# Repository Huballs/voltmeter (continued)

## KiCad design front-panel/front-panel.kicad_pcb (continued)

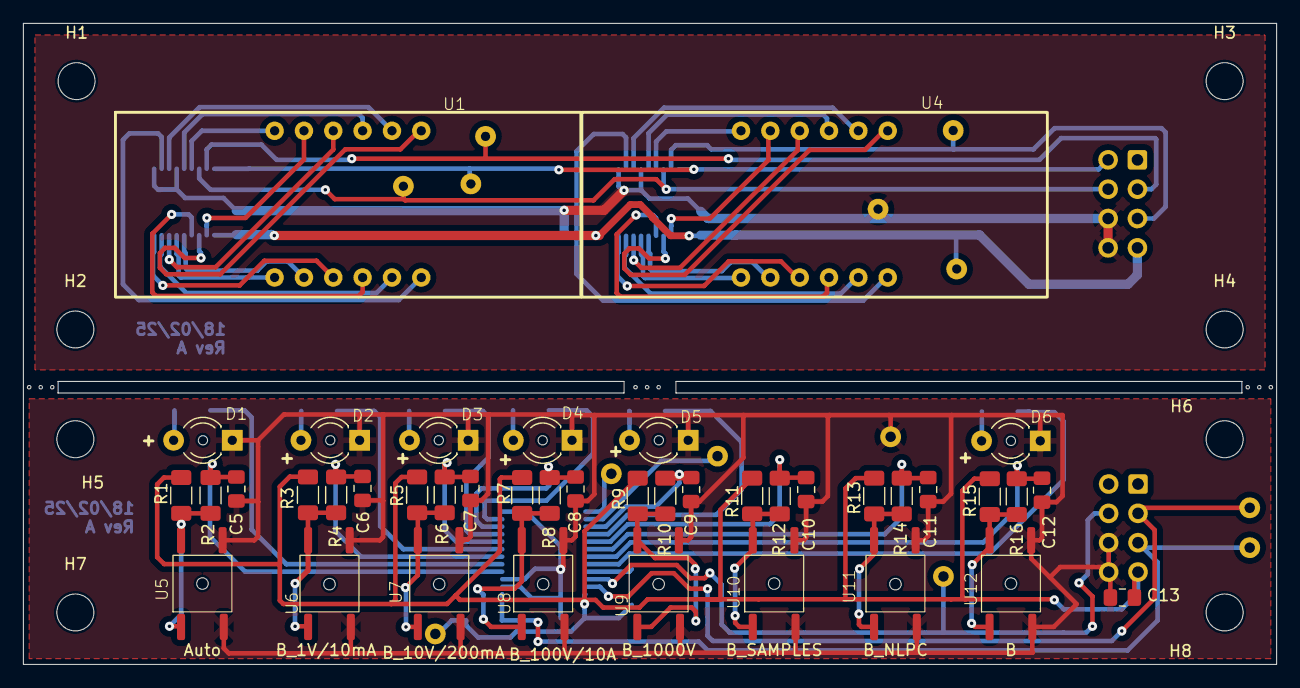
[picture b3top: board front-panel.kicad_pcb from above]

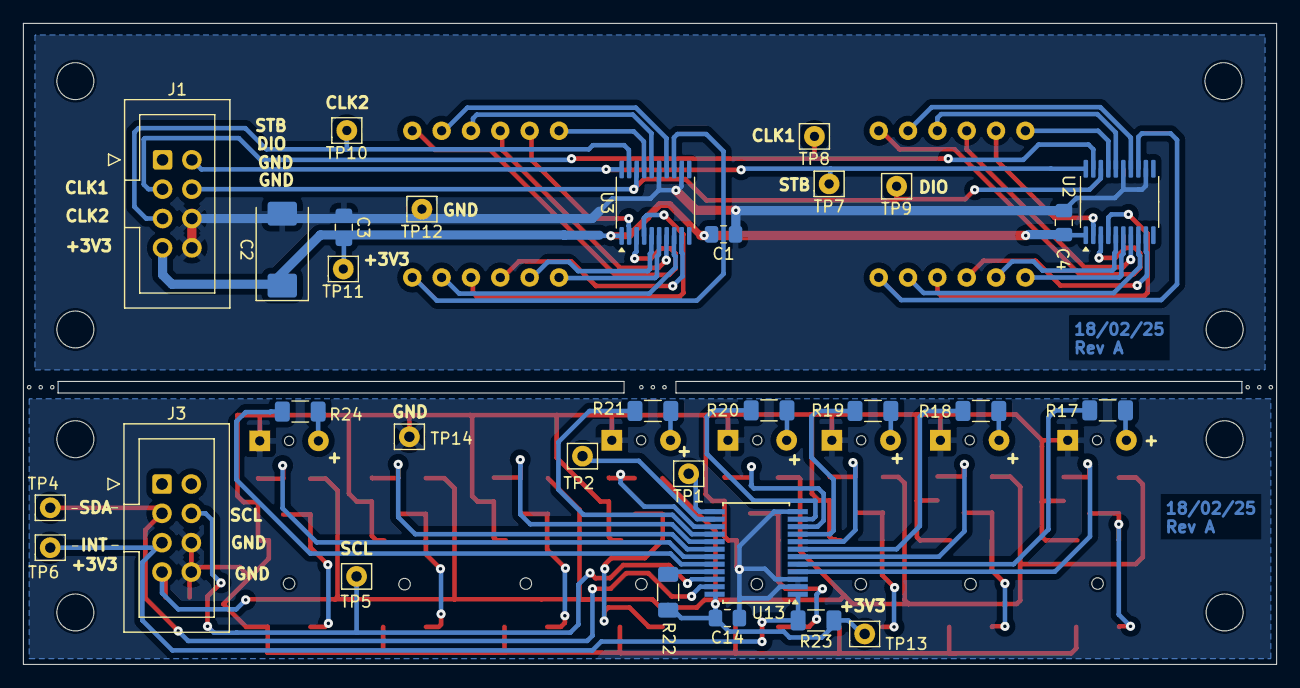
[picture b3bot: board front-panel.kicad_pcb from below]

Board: 2 copper layers, 108.5 x 55.5 mm, 88 parts (31 on the bottom side), 66 nets.

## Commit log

2025-02-06 init
2025-02-07 folders fix
2025-02-07 ref done
2025-02-07 starting pcb
